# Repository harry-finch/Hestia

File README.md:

# Hestia
A battery powered WiFi temperature sensor. The name comes from the ancient greek goddess of the hearth.

Because of its rather simple function (showing the temperature), this board can also serve as a base for other IOT projects. It embeds many basic features:
- USB to UART (CH340G)
- Auto-reset for code upload
- Li-Ion battery management (MCP73831)
- Battery level indicator
- Load sharing between battery and USB
- ESP8266 minimal wiring

The schematic should be easily customizable for other projects.

## Temperature sensor
This project uses the MCP9808 chip to measure the temperature. The reason for choosing this IC is because it uses I2C and will provide a more accurate reading than the MCU's ADC.

## Display
The board features 4 holes to wire a 0.91 inch OLED display. 

## Casing
The casing can be 3D printed.

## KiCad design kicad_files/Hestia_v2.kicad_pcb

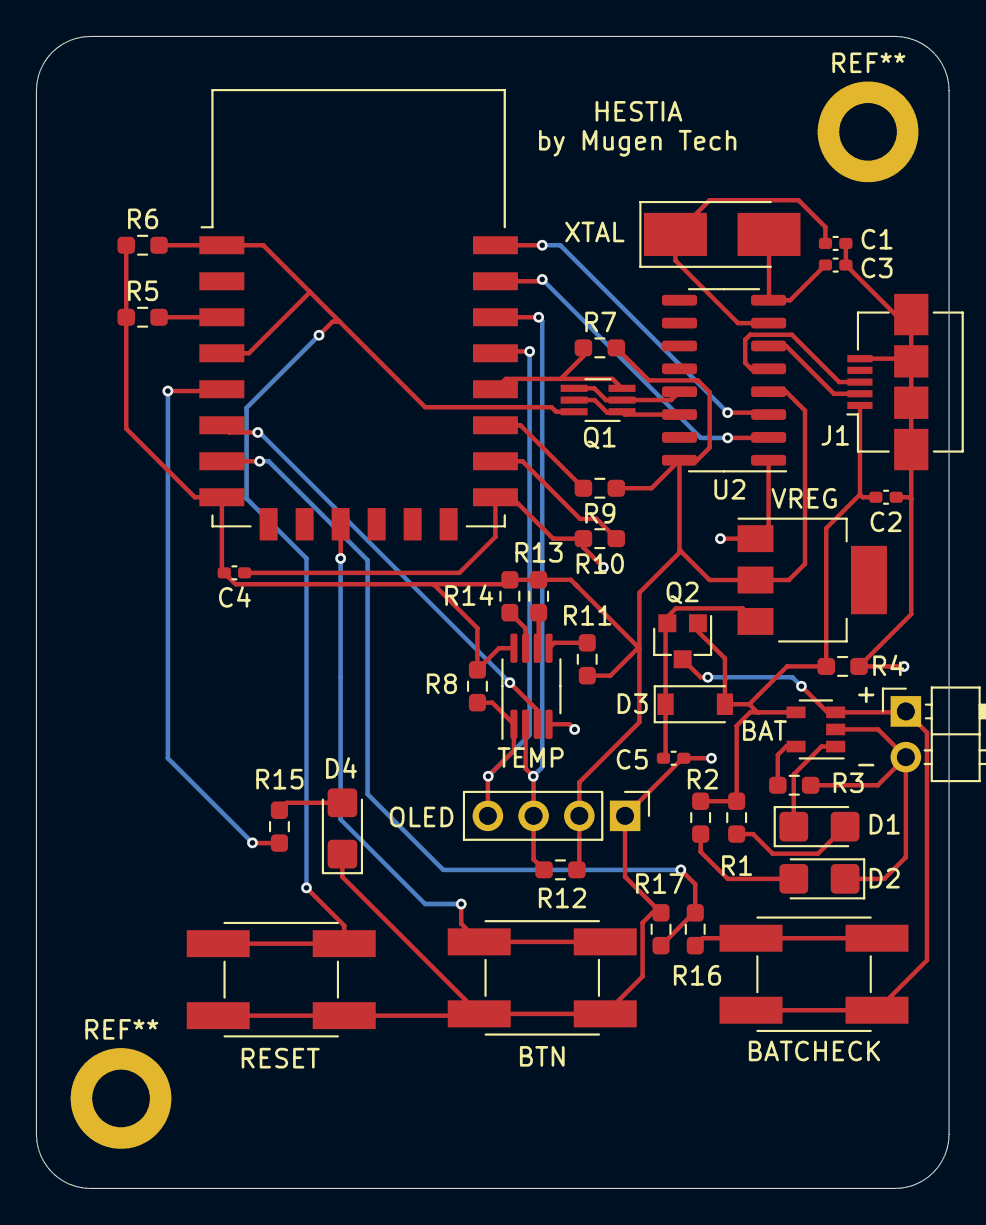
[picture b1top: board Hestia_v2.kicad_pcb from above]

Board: 2 copper layers, 50.7 x 64.0 mm, 40 parts (0 on the bottom side), 33 nets.

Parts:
BAT: MCP73831-2-OT; SOT-23-5
BATCHECK: BUTTON_B3SN; Button_Omron_B3SN_6x6mm
BTN: BUTTON_B3SN; Button_Omron_B3SN_6x6mm
C1, C3: 22p; C_0402_1005Metric_Pad0.74x0.62mm_HandSolder
C2: 4.7u; C_0402_1005Metric_Pad0.74x0.62mm_HandSolder
C4, C5: 1u; C_0402_1005Metric_Pad0.74x0.62mm_HandSolder
D1, D2, D4: LED; LED_1206_3216Metric_Castellated
D3: D_Schottky; D_SOD-123
J1: USB_B_Micro; USB_Micro-B_Amphenol_10104110_Horizontal
J2: Conn_01x02; PinHeader_1x02_P2.54mm_Horizontal
OLED: OLED; PinHeader_1x04_P2.54mm_Vertical
Q1: UMH3N; SOT-363_SC-70-6_Handsoldering
Q2: MOSFET_P-CH_30V_1.1A; SOT-23
R1, R2, R15: 470; R_0603_1608Metric_Pad0.98x0.95mm_HandSolder
R3, R5, R6, R7, R8, R9, R10, R11, R12, R13, R14: 10K; R_0603_1608Metric_Pad0.98x0.95mm_HandSolder
R4: 100K; R_0603_1608Metric_Pad0.98x0.95mm_HandSolder
R16: 6.8K; R_0603_1608Metric_Pad0.98x0.95mm_HandSolder
R17: 2.2K; R_0603_1608Metric_Pad0.98x0.95mm_HandSolder
RESET: BUTTON_B3SN; Button_Omron_B3SN_6x6mm
TEMP: MCP9808_MSOP; MSOP-8_3x3mm_P0.65mm
U2: CH340G; SOIC-16_3.9x9.9mm_P1.27mm
U4: ESP-12E
VREG: LM1117-3.3; SOT-223
XTAL: Crystal; Crystal_SMD_5032-2Pin_5.0x3.2mm_HandSoldering

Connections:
+3V3: C4.1, OLED.2, R5.1, R6.1, R7.1, R8.2, R9.1, R11.2, R12.2, R13.2, R14.2, TEMP.8, U2.4, U2.16, U4.8, VREG.2
+5V: BAT.4, C2.1, D3.2, J1.1, Q2.1, R1.1, R2.1, R4.2
ALERT: TEMP.3, U4.6
BTN: BTN.1, U4.11
CHECKBAT: R16.2, R17.1, U4.7
DTR: Q1.2, Q1.4, U2.13
GND: BAT.2, BTN.2, C1.2, C2.2, C3.2, C4.2, C5.2, D2.1, D4.1, J1.5, J1.6, J2.2, OLED.1, R3.2, R4.1, R10.2, R17.2, RESET.2, TEMP.4, U2.1, U4.15, VREG.1
IO0: Q1.3, R7.2, U4.18
LED: R15.2, U4.5
unnamed: C1.1, U2.7, XTAL.1
unnamed: C3.1, U2.8, XTAL.2
unnamed: D1.2, R1.2
unnamed: D2.2, R2.2
unnamed: D4.2, R15.1
unnamed: J1.2, U2.6
unnamed: J1.3, U2.5
unnamed: BAT.5, R3.1
unnamed: R5.2, U4.3
unnamed: R9.2, U4.17
unnamed: R10.1, U4.16
unnamed: R11.1, TEMP.5
unnamed: R13.1, TEMP.6
unnamed: R14.1, TEMP.7
unnamed: BATCHECK.2, R16.1
RESET: Q1.6, R6.2, RESET.1, U4.1, U4.4
RTS: Q1.1, Q1.5, U2.14
RX: U2.2, U4.21
SCL: OLED.3, R12.1, TEMP.2, U4.20
SDA: OLED.4, R8.1, TEMP.1, U4.19
STAT: BAT.1, D1.1
TX: U2.3, U4.22
VBAT: BAT.3, BATCHECK.1, J2.1, Q2.3
VCC: C5.1, D3.1, Q2.2, VREG.3
